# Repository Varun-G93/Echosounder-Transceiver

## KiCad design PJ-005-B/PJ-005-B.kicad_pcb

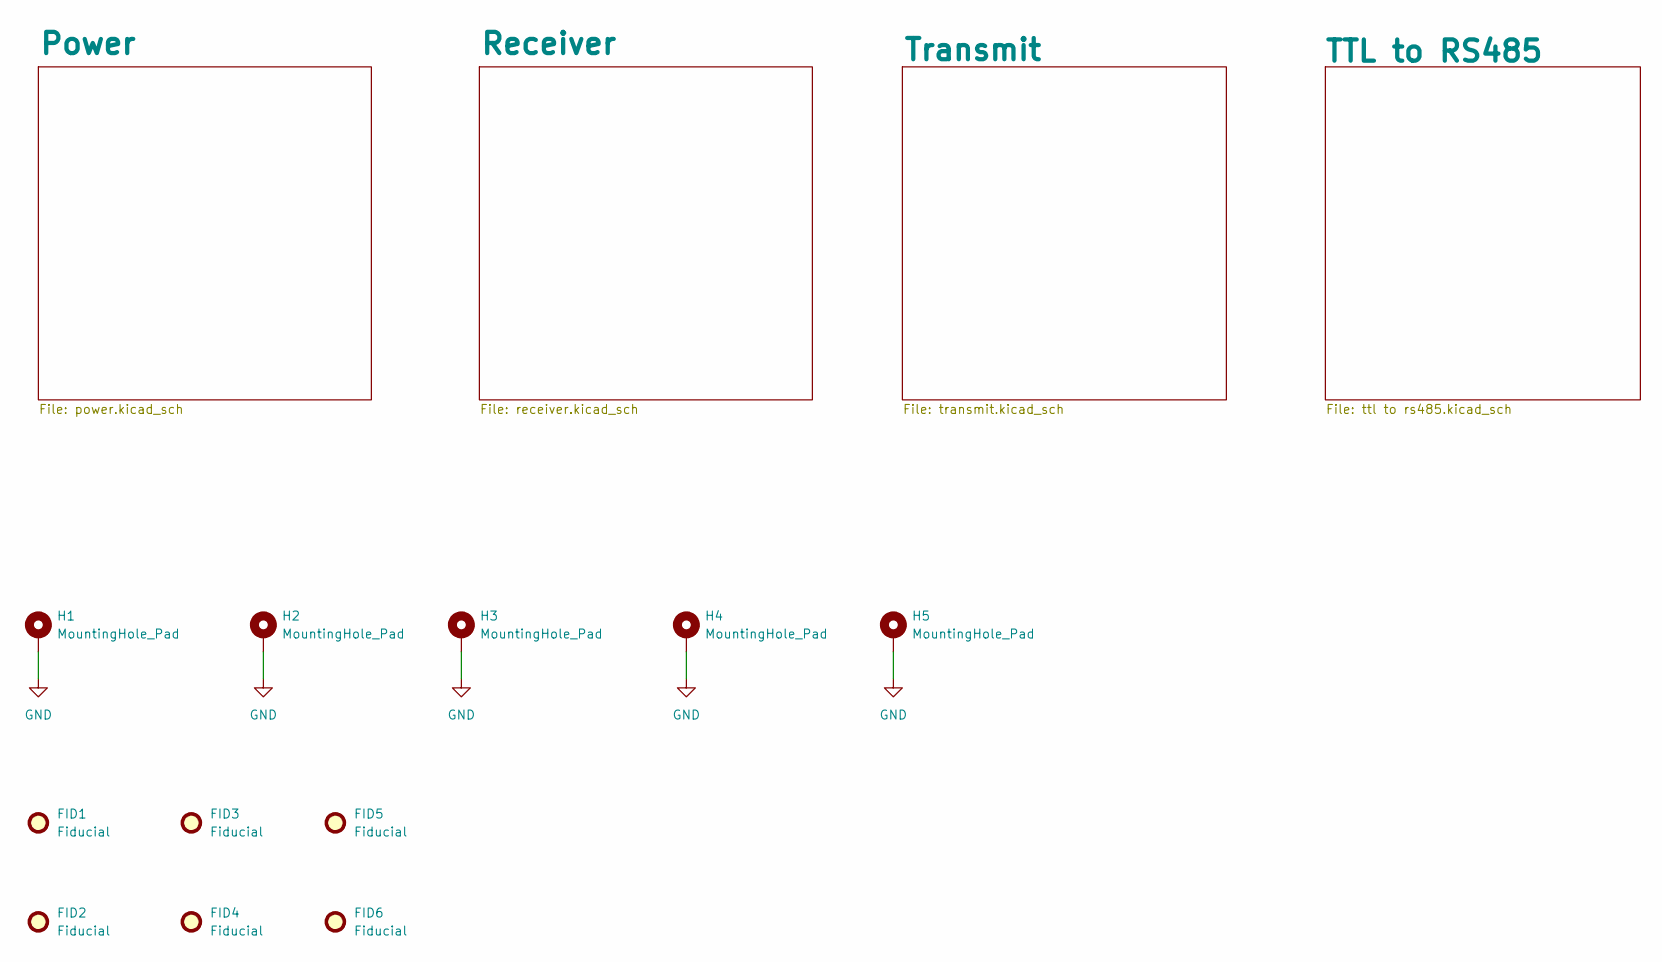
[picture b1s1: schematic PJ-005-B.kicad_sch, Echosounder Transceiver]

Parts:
FID1, FID2, FID3, FID4, FID5, FID6: Fiducial; Fiducial_0.5mm_Mask1mm
H1, H2, H3, H4, H5: MountingHole_Pad; MountingHole_3.2mm_M3_DIN965_Pad

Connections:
GND: H1.1, H2.1, H3.1, H4.1, H5.1; also elsewhere on the board

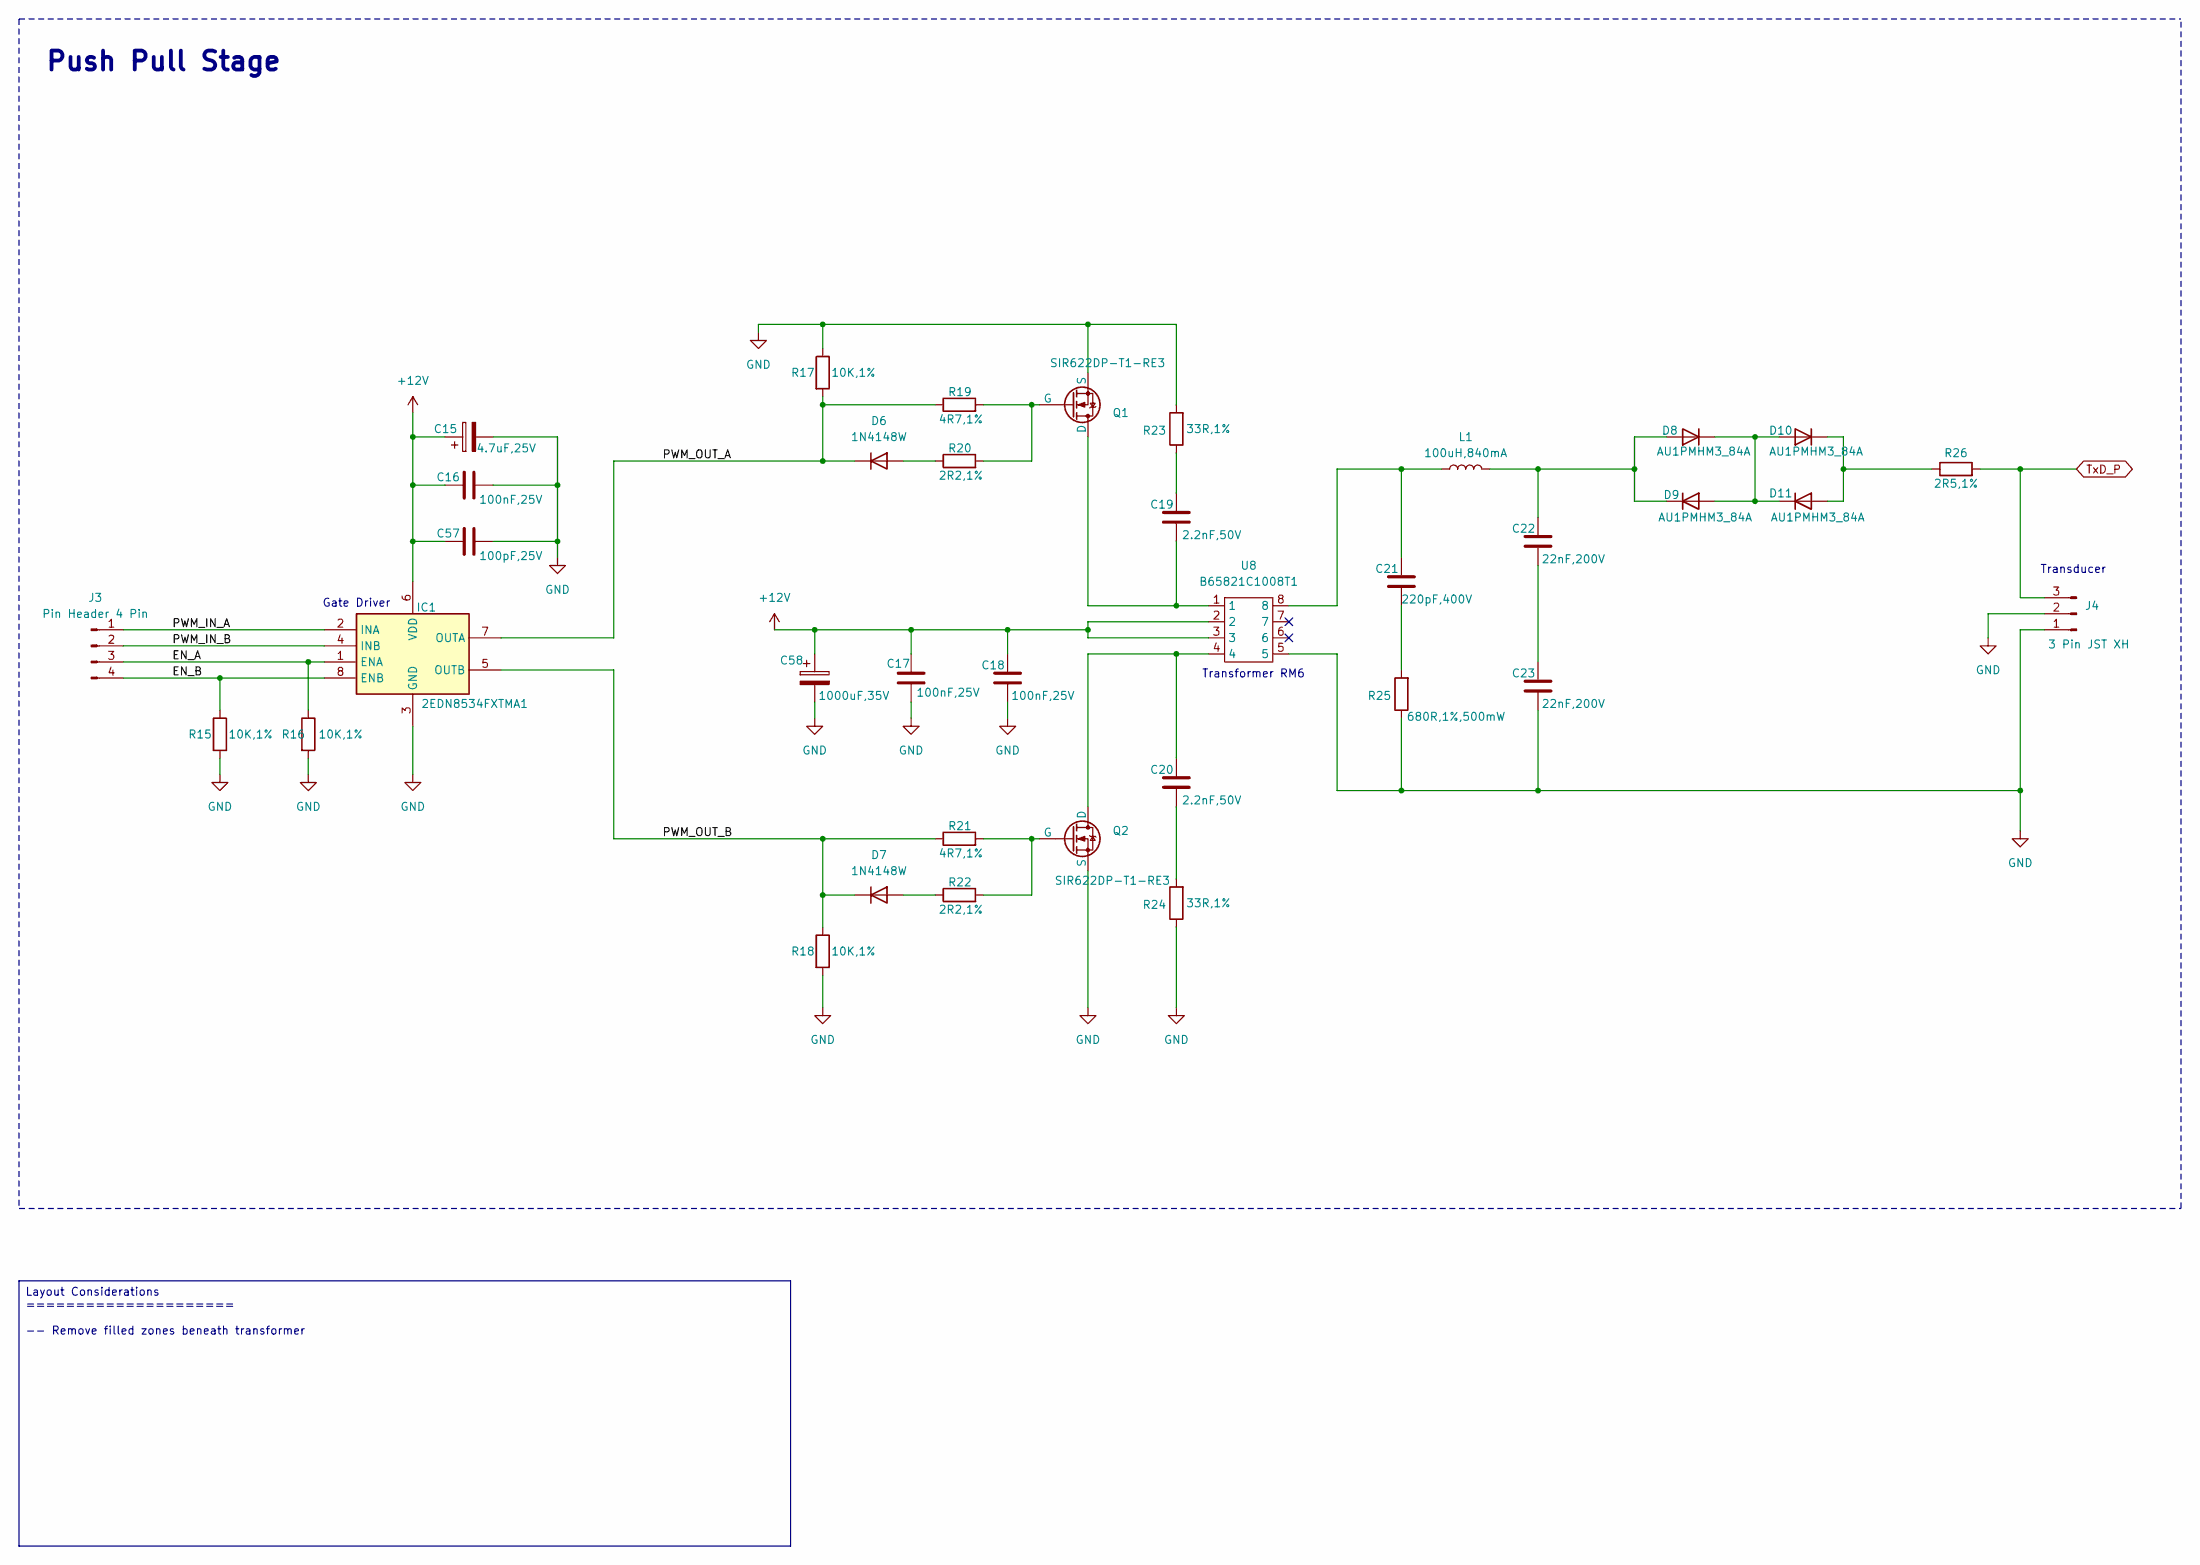
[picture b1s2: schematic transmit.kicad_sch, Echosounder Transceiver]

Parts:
C15: 4.7uF,25V; C1206; ManufacturerPartNumber TAJA475K025RNJ
C16, C17, C18: 100nF,25V; C0603
C19, C20: 2.2nF,50V; C0603
C21: 220pF,400V; C0603
C22, C23: 22nF,200V; C0603
C57: 100pF,25V; C0603
C58: 1000uF,35V; CP_Radial_D8.0mm_P3.50mm; ManufacturerPartNumber EEUFR1C102LJ
D6, D7: 1N4148W; SOD-123; ManufacturerPartNumber 1N4148W
D8, D9, D10, D11: AU1PMHM3_84A; AU1PMHM384A; ManufacturerPartNumber AU1PMHM3_84A
IC1: 2EDN8534FXTMA1; SOIC127P602X173-8N; ManufacturerPartNumber 2EDN8534FXTMA1
J3: Pin Header 4 Pin; PinHeader_1x04_P2.54mm_Vertical
J4: 3 Pin JST XH; JST_XH_B3B-XH-A_1x03_P2.50mm_Vertical
L1: 100uH,840mA; INDPM4040X300N; ManufacturerPartNumber ASPI-4030S-330M-T
Q1, Q2: SIR622DP-T1-RE3; SIR622DPT1RE3; ManufacturerPartNumber SIR622DP-T1-RE3
R15, R16, R17, R18: 10K,1%; R0603
R19, R21: 4R7,1%; R0603
R20, R22: 2R2,1%; R0603
R23, R24: 33R,1%; R0603
R25: 680R,1%,500mW; R0603
R26: 2R5,1%; R0603
U8: B65821C1008T1; RM6; ManufacturerPartNumber B65821C1008T1

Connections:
+12V: C15.1, C16.2, C17.1, C18.1, C57.2, C58.1, IC1.6 (VDD), U8.2, U8.3; also elsewhere on the board
/Transmit/EN_A: IC1.1 (ENA), J3.3, R16.1
/Transmit/EN_B: IC1.8 (ENB), J3.4, R15.1
/Transmit/PWM_IN_A: IC1.2 (INA), J3.1
/Transmit/PWM_IN_B: IC1.4 (INB), J3.2
/Transmit/PWM_OUT_A: D6.1 (K), IC1.7 (OUTA), R17.2, R19.1
/Transmit/PWM_OUT_B: D7.1 (K), IC1.5 (OUTB), R18.1, R21.1
GND: C15.2, C16.1, C17.2, C18.2, C23.2, C57.1, C58.2, IC1.3 (GND), J4.1, J4.2, Q1.2 (S), Q2.2 (S), R15.2, R16.2, R17.1, R18.2, R23.2, R24.1, R25.1, U8.5; also elsewhere on the board
unnamed: C19.1, R23.1
unnamed: C20.2, R24.2
unnamed: C21.1, L1.1, U8.8
unnamed: C21.2, R25.2
unnamed: C22.2, C23.1
unnamed: D6.2 (A), R20.1
unnamed: D7.2 (A), R22.1
unnamed: C22.1, D8.2 (A), D9.1 (K), L1.2
unnamed: D8.1 (K), D9.2 (A), D10.2 (A), D11.1 (K)
unnamed: D10.1 (K), D11.2 (A), R26.1
unnamed: C19.2, Q1.3 (D), U8.1
unnamed: Q1.1 (G), R19.2, R20.2
unnamed: C20.1, Q2.3 (D), U8.4
unnamed: Q2.1 (G), R21.2, R22.2
TxD_P: J4.3, R26.2; also elsewhere on the board

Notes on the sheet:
Transducer
Gate Driver
Push Pull Stage
Transformer RM6
Layout Considerations ===================== -- Remove filled zones beneath transformer

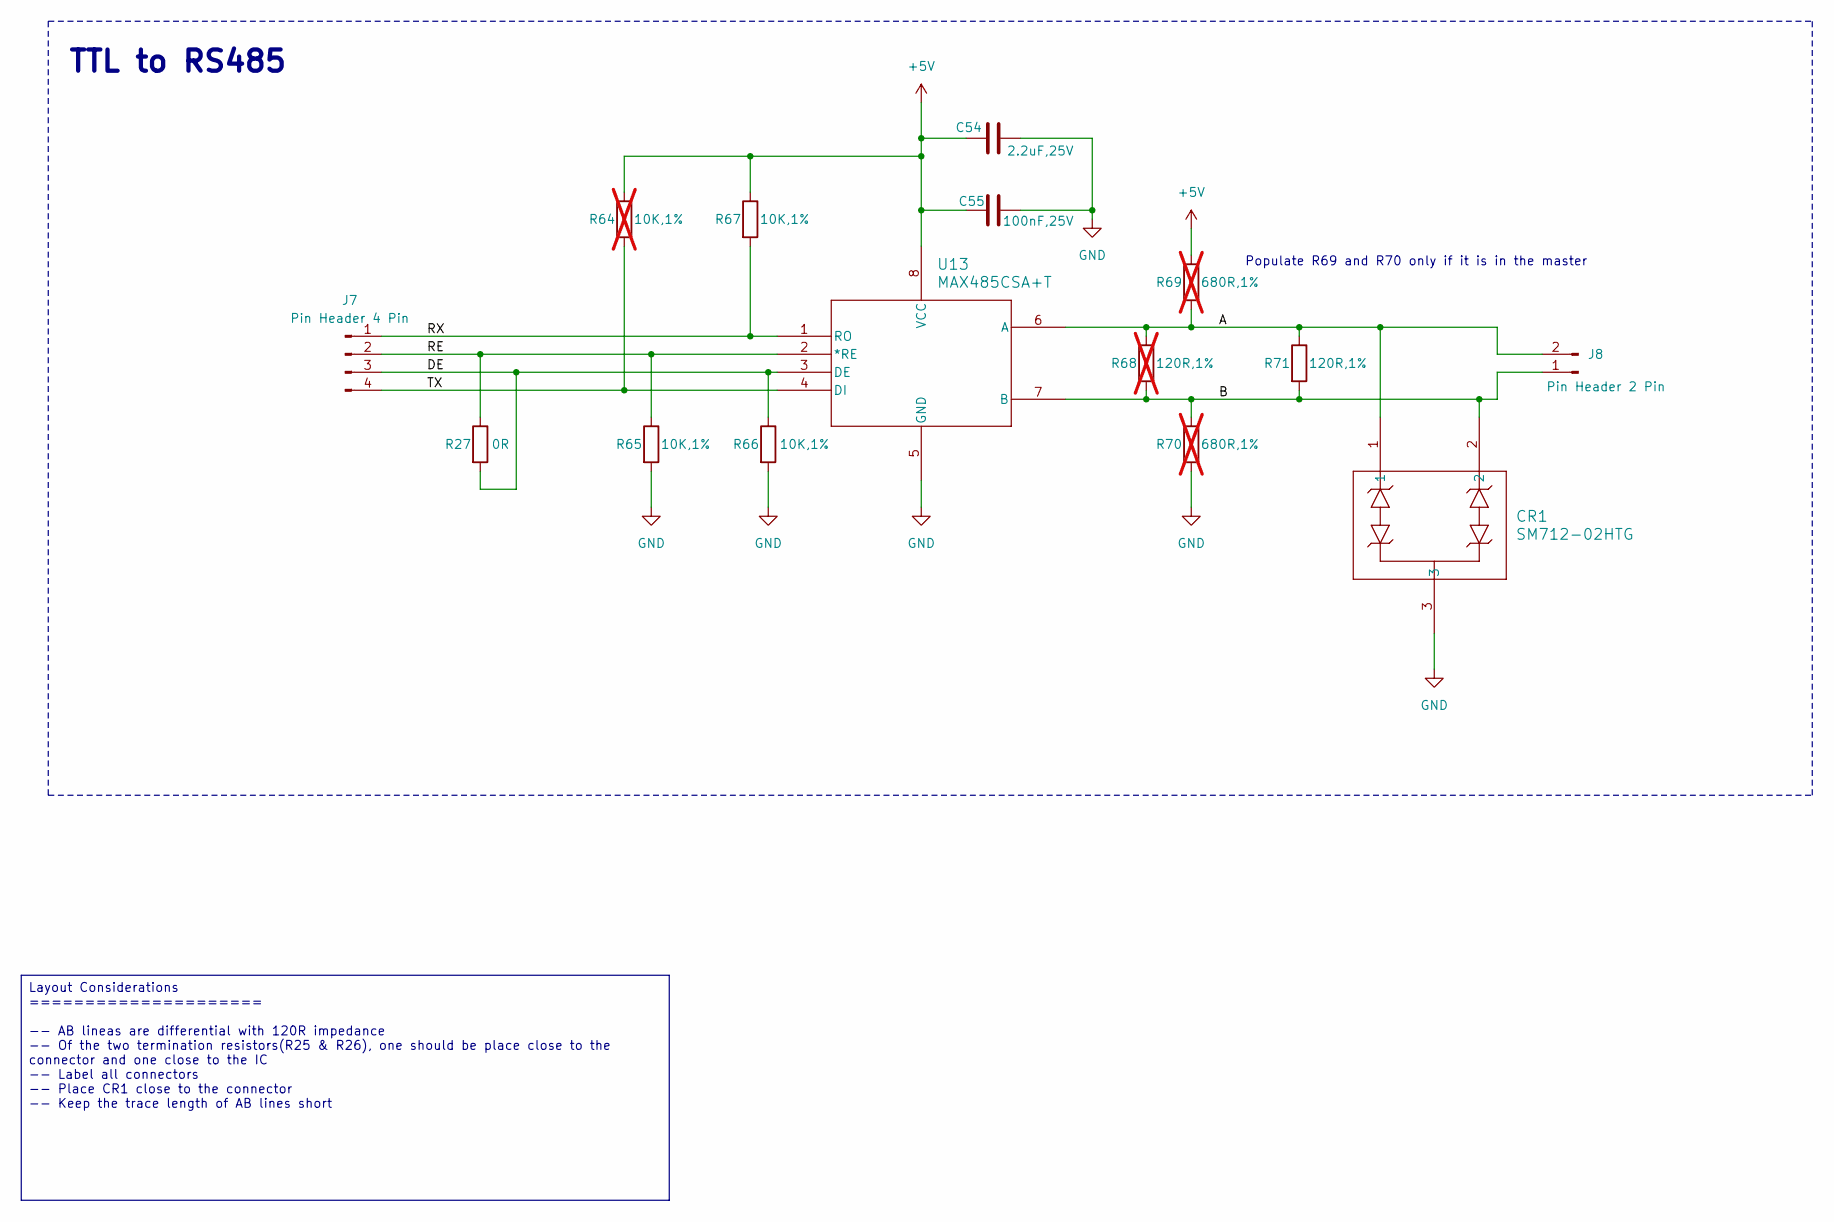
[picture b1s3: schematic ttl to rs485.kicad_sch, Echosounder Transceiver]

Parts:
C54: 2.2uF,25V; C0603
C55: 100nF,25V; C0603
CR1: SM712-02HTG; SOT-23-3; ManufacturerPartNumber SM712-02HTG
J7: Pin Header 4 Pin; PinHeader_1x04_P2.54mm_Vertical
J8: Pin Header 2 Pin; PinHeader_1x02_P2.54mm_Vertical
R27: 0R; R0603
R64: 10K,1%; R0603; not fitted
R65, R66, R67: 10K,1%; R0603
R68: 120R,1%; R0603; not fitted
R69, R70: 680R,1%; R0603; not fitted
R71: 120R,1%; R0603
U13: MAX485CSA+T; SOIC-8-5.3x5.3x1.27; ManufacturerPartNumber MAX485CSA+T

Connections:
+5V: C54.1, C55.1, R64.1, R67.1, R69.1, U13.8 (VCC); also elsewhere on the board
/TTL to RS485/A: CR1.1, J8.2, R68.1, R69.2, R71.1, U13.6 (A)
/TTL to RS485/B: CR1.2, J8.1, R68.2, R70.1, R71.2, U13.7 (B)
/TTL to RS485/DE: J7.3, R27.2, R66.1, U13.3 (DE)
/TTL to RS485/RE: J7.2, R27.1, R65.1, U13.2 (*RE)
/TTL to RS485/RX: J7.1, R67.2, U13.1 (RO)
/TTL to RS485/TX: J7.4, R64.2, U13.4 (DI)
GND: C54.2, C55.2, CR1.3, R65.2, R66.2, R70.2, U13.5 (GND); also elsewhere on the board

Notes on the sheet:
TTL to RS485
Populate R69 and R70 only if it is in the master
Layout Considerations ===================== -- AB lineas are differential with 120R impedance -- Of the two termination resistors(R25 & R26), one should be place close to the connector and one close to the IC -- Label all connectors -- Place CR1 close to the connector -- Keep the trace length of AB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

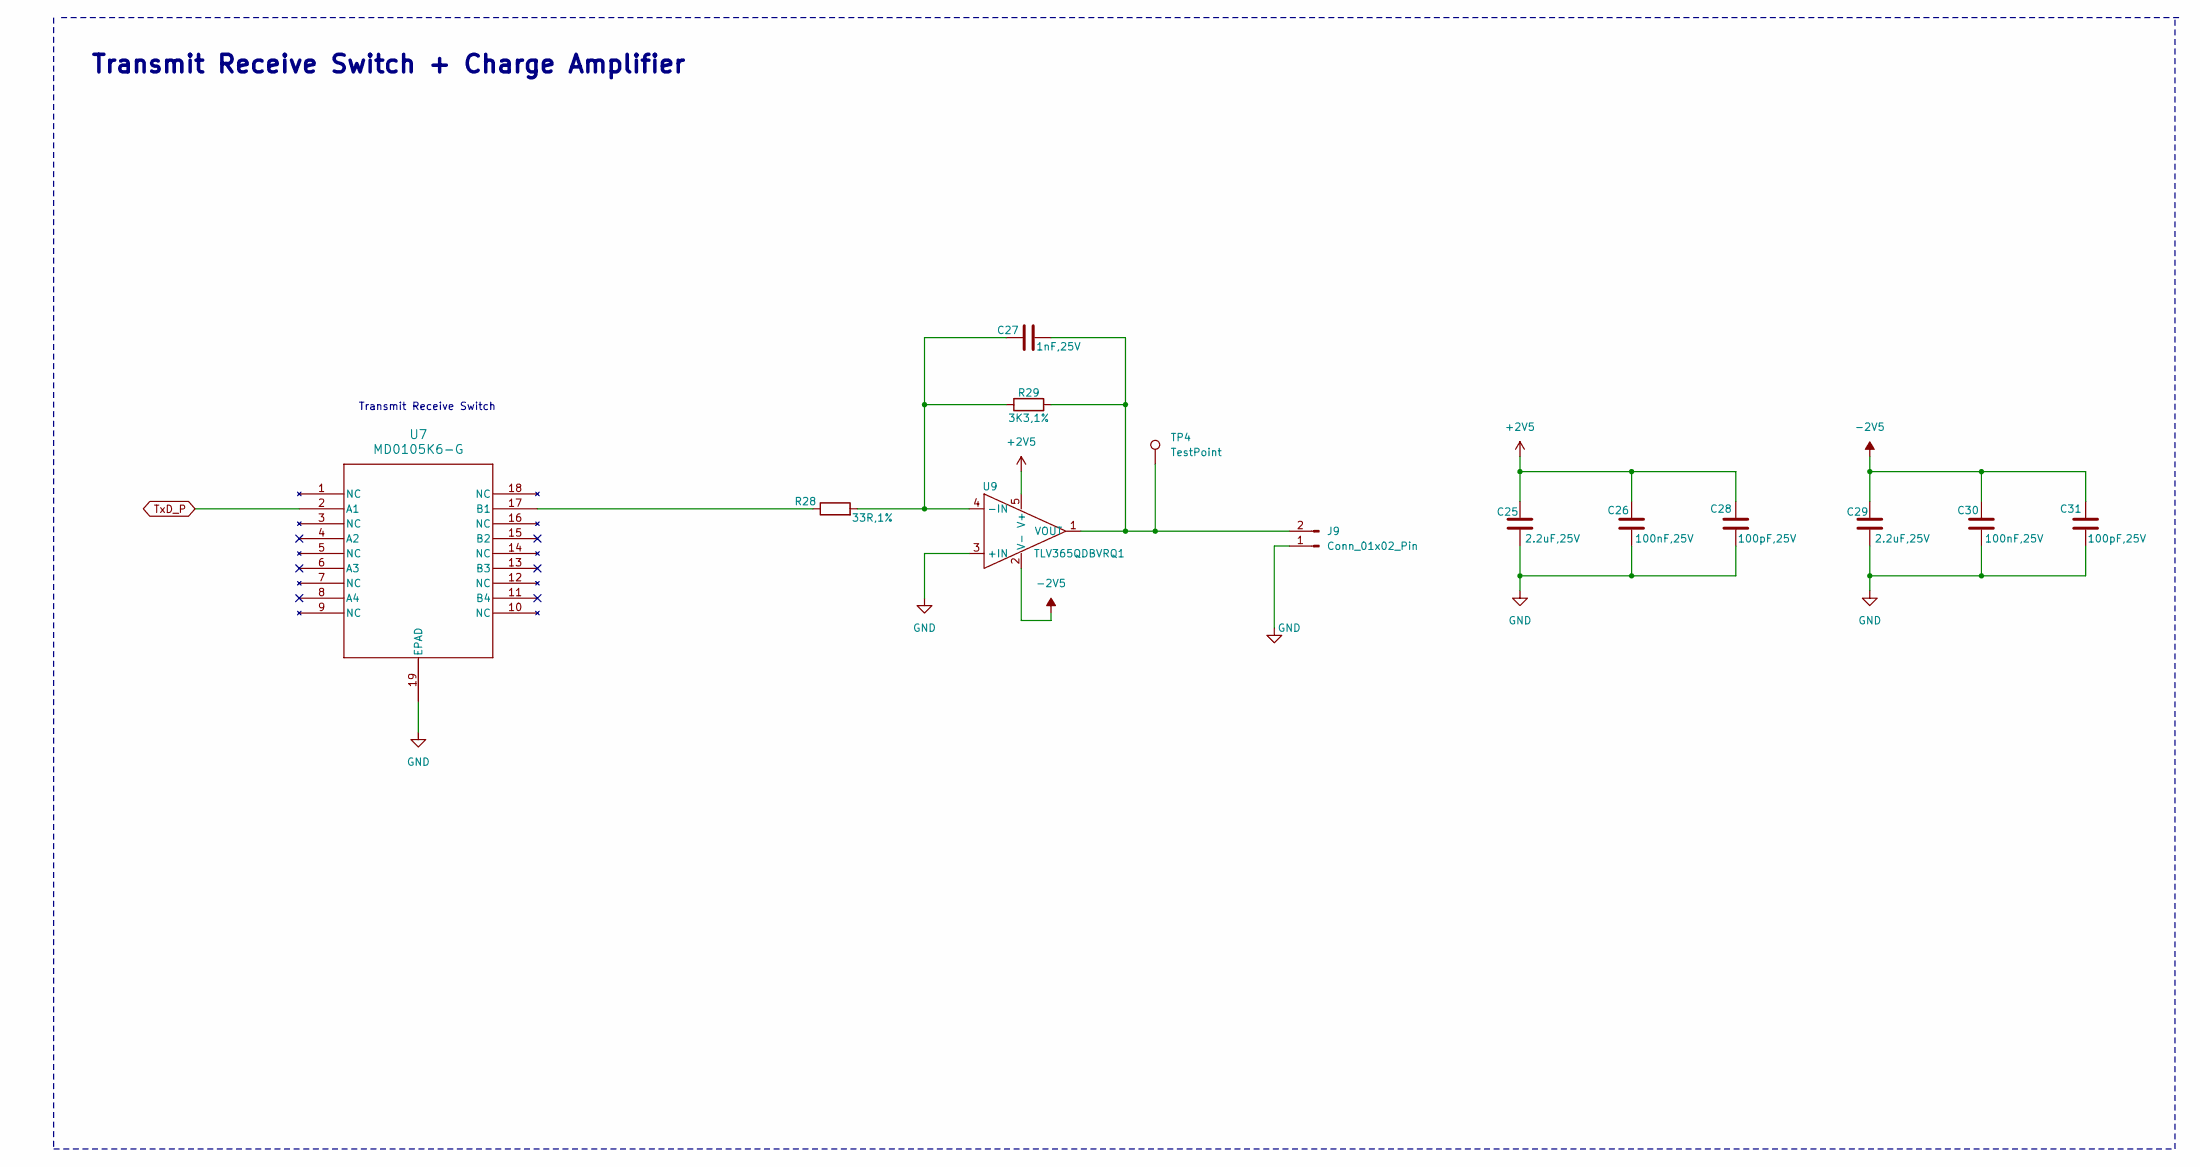
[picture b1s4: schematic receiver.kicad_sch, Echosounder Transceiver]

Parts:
C25, C29: 2.2uF,25V; C0603
C26, C30: 100nF,25V; C0603
C27: 1nF,25V; C0603
C28, C31: 100pF,25V; C0603
J9: Conn_01x02_Pin; PinHeader_1x02_P2.54mm_Vertical
R28: 33R,1%; R0603
R29: 3K3,1%; R0603
TP4: TestPoint; TestPoint_Pad_1.0x1.0mm
U7: MD0105K6-G; DFN18; ManufacturerPartNumber MD0105K6-G
U9: TLV365QDBVRQ1; SOT-23-5; ManufacturerPartNumber TLV365QDBVRQ1

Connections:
+2V5: C25.1, C26.2, C28.2, U9.5 (V+); also elsewhere on the board
-2V5: C29.1, C30.2, C31.2, U9.2 (V-); also elsewhere on the board
GND: C25.2, C26.1, C28.1, C29.2, C30.1, C31.1, J9.1, U7.19 (EPAD), U9.3 (+IN); also elsewhere on the board
unnamed: C27.2, J9.2, R29.2, TP4.1, U9.1 (VOUT)
unnamed: R28.1, U7.17 (B1)
unnamed: C27.1, R28.2, R29.1, U9.4 (-IN)
TxD_P: U7.2 (A1); also elsewhere on the board

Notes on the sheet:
Transmit Receive Switch
Transmit Receive Switch + Charge Amplifier

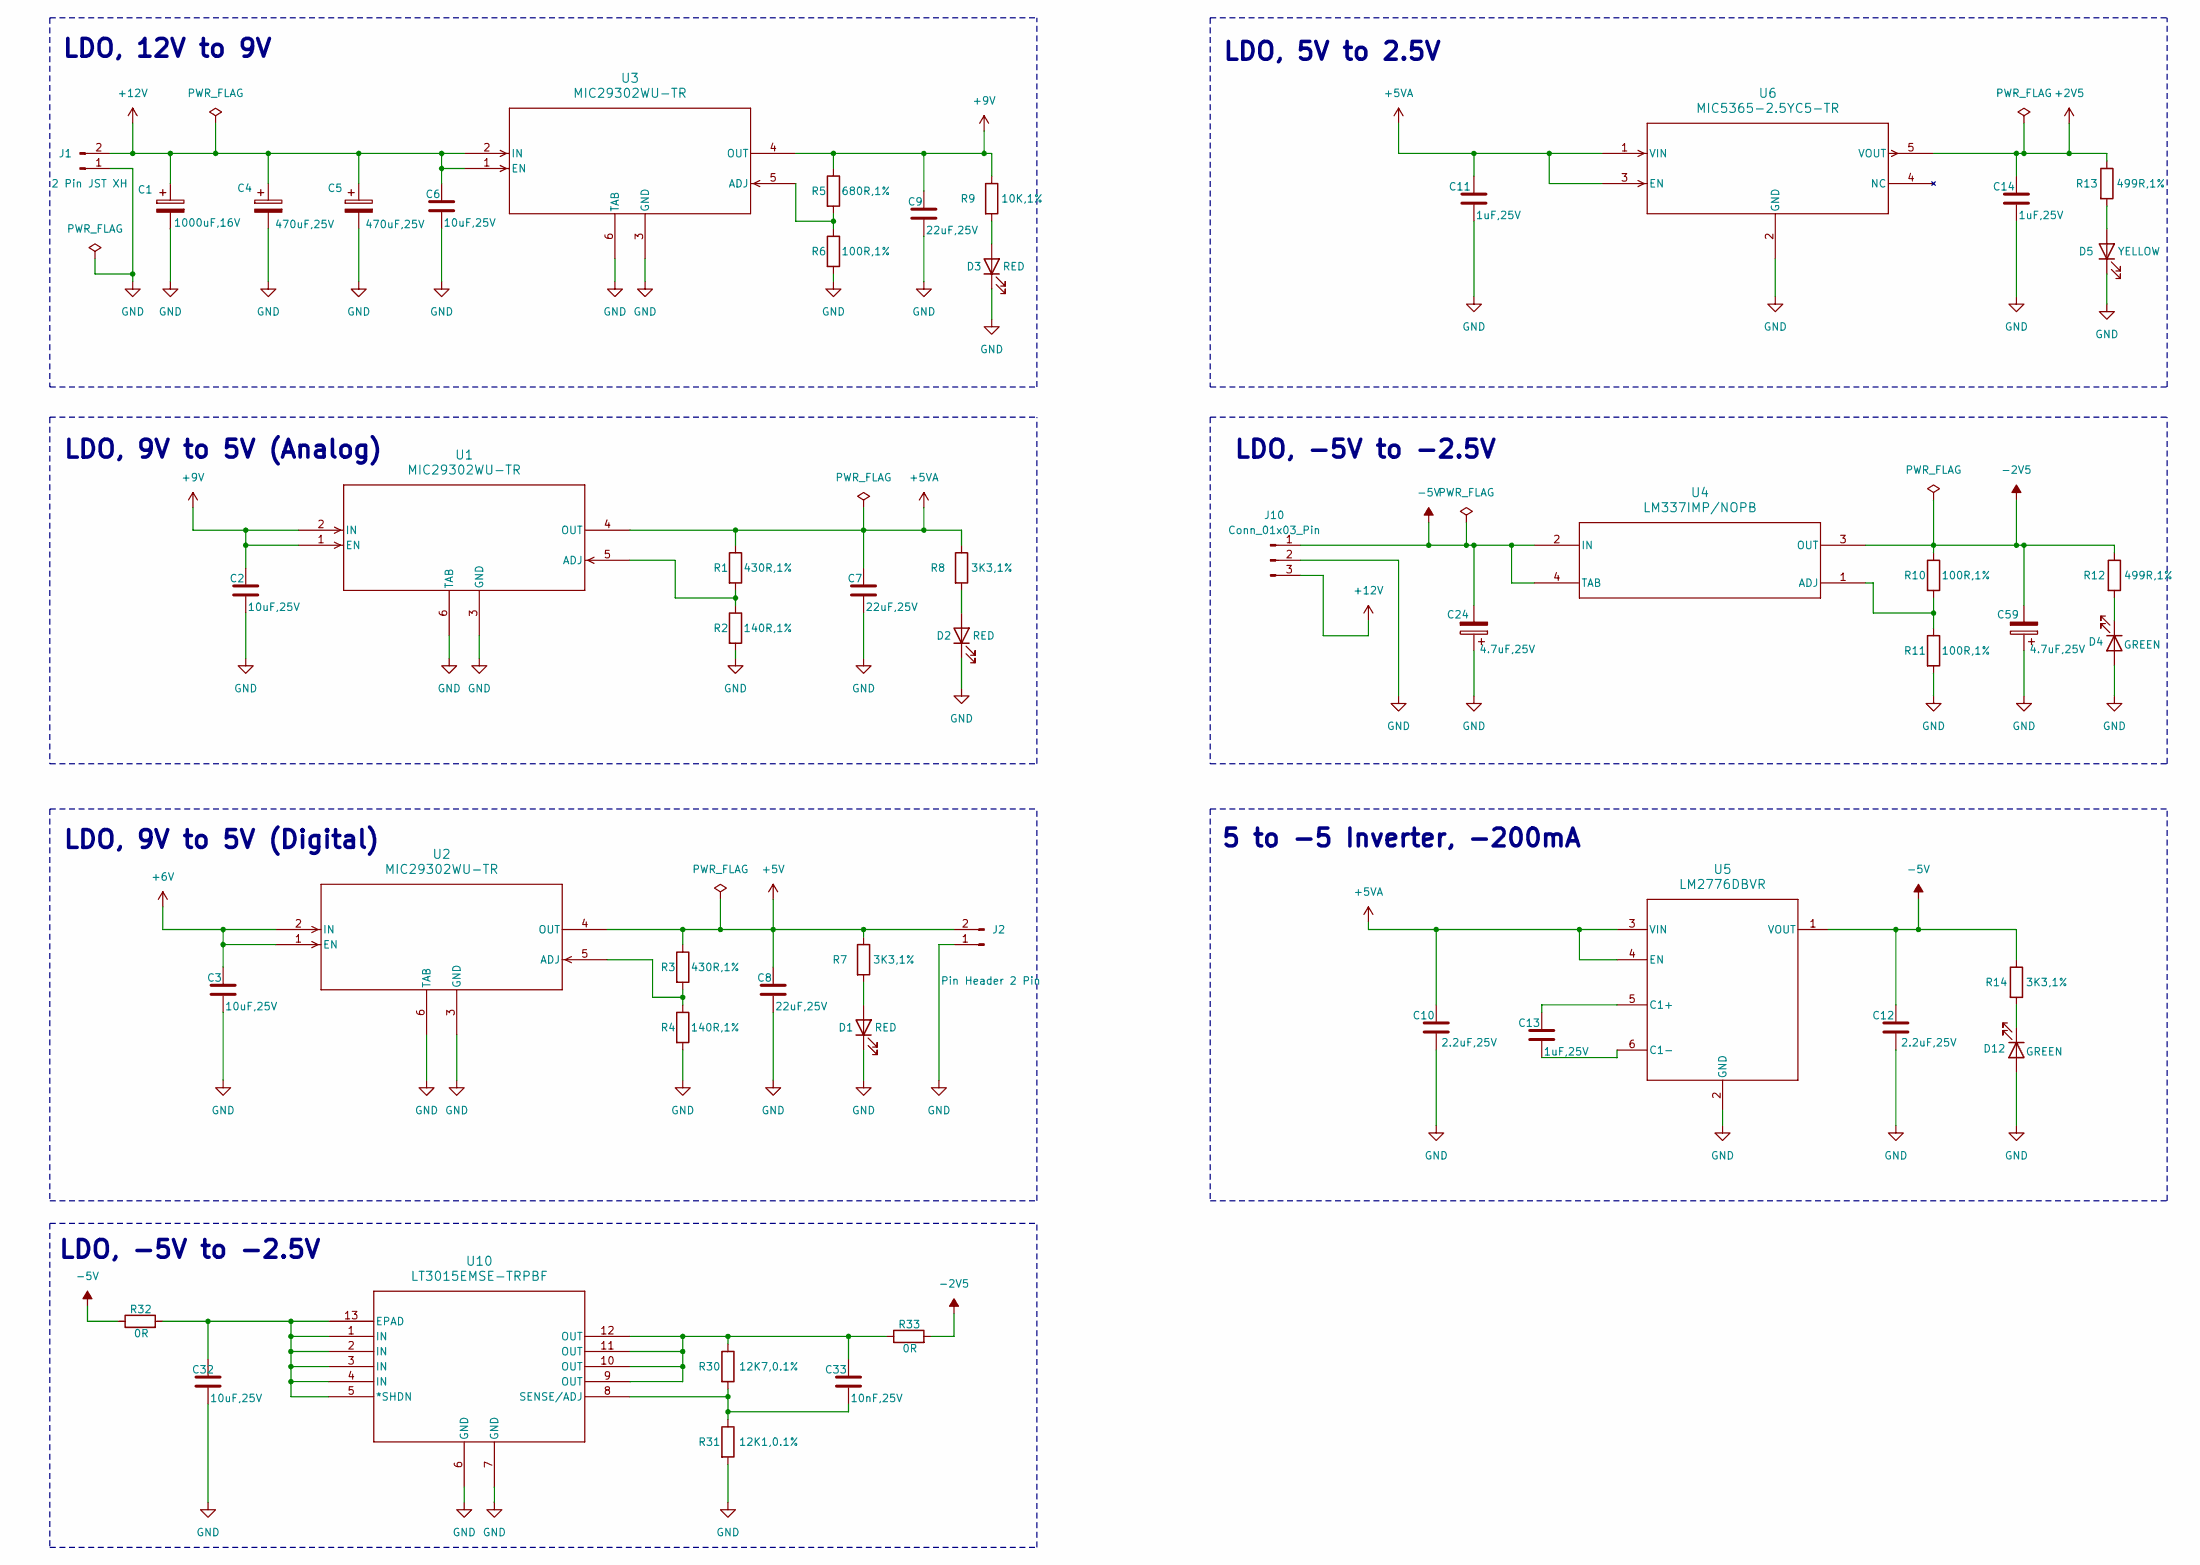
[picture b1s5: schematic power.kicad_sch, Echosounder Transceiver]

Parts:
C1: 1000uF,16V; CP_Radial_D8.0mm_P3.50mm; ManufacturerPartNumber EEUFR1C102LJ
C2, C3, C6, C32: 10uF,25V; C0603
C4, C5: 470uF,25V; CP_Radial_D8.0mm_P3.50mm; ManufacturerPartNumber RET0816471M025B
C7, C8, C9: 22uF,25V; C0603
C10, C12: 2.2uF,25V; C0603
C11, C13, C14: 1uF,25V; C0603
C24, C59: 4.7uF,25V; C1206; ManufacturerPartNumber TAJA475K025RNJ
C33: 10nF,25V; C0603
D1, D2, D3: RED; LED_0603_1608Metric
D4, D12: GREEN; LED_0603_1608Metric
D5: YELLOW; LED_0603_1608Metric
J1: 2 Pin JST XH; JST_XH_B2B-XH-A_1x02_P2.50mm_Vertical
J2: Pin Header 2 Pin; PinHeader_1x02_P2.54mm_Vertical
J10: Conn_01x03_Pin; PinHeader_1x03_P2.54mm_Vertical
R1, R3: 430R,1%; R0603
R2, R4: 140R,1%; R0603
R5: 680R,1%; R0603
R6, R10, R11: 100R,1%; R0603
R7, R8, R14: 3K3,1%; R0603
R9: 10K,1%; R0603
R12, R13: 499R,1%; R0603
R30: 12K7,0.1%; R0603
R31: 12K1,0.1%; R0603
R32, R33: 0R; R0603
U1, U2, U3: MIC29302WU-TR; TO-263-5; ManufacturerPartNumber MIC29302WU-TR
U4: LM337IMP/NOPB; SOT-223; ManufacturerPartNumber LM337IMP/NOPB
U5: LM2776DBVR; SOT23-6; ManufacturerPartNumber LM2776DBVR
U6: MIC5365-2.5YC5-TR; SC-70; ManufacturerPartNumber MIC5365-2.5YC5-TR
U10: LT3015EMSE-TRPBF; MSOP-12; ManufacturerPartNumber LT3015EMSE-TRPBF

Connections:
+2V5: C14.1, R13.1, U6.5 (VOUT); also elsewhere on the board
+5V: C8.1, J2.2, R3.1, R7.1, U2.4 (OUT); also elsewhere on the board
+5VA: C7.1, C10.1, C11.1, R1.1, R8.1, U1.4 (OUT), U5.3 (VIN), U5.4 (EN), U6.1 (VIN), U6.3 (EN)
+6V: C3.1, U2.1 (EN), U2.2 (IN)
+9V: C2.1, C9.1, R5.1, R9.1, U1.1 (EN), U1.2 (IN), U3.4 (OUT)
+12V: C1.1, C4.1, C5.1, C6.1, J1.2, J10.3, U3.1 (EN), U3.2 (IN); also elsewhere on the board
-2V5: C59.2, R10.1, R12.1, R33.2, U4.3 (OUT); also elsewhere on the board
-5V: C12.1, C24.2, J10.1, R14.1, R32.1, U4.2 (IN), U4.4 (TAB), U5.1 (VOUT)
GND: C1.2, C2.2, C3.2, C4.2, C5.2, C6.2, C7.2, C8.2, C9.2, C10.2, C11.2, C12.2, C14.2, C24.1, C32.2, C59.1, D1.1 (K), D2.1 (K), D3.1 (K), D4.2 (A), D5.1 (K), D12.2 (A), J1.1, J2.1, J10.2, R2.2, R4.2, R6.2, R11.2, R31.2, U1.3 (GND), U1.6 (TAB), U2.3 (GND), U2.6 (TAB), U3.3 (GND), U3.6 (TAB), U5.2 (GND), U6.2 (GND), U10.6 (GND), U10.7 (GND); also elsewhere on the board
unnamed: C33.1, R30.1, R33.1, U10.9 (OUT), U10.10 (OUT), U10.11 (OUT), U10.12 (OUT)
unnamed: D1.2 (A), R7.2
unnamed: D2.2 (A), R8.2
unnamed: D3.2 (A), R9.2
unnamed: D4.1 (K), R12.2
unnamed: D5.2 (A), R13.2
unnamed: D12.1 (K), R14.2
unnamed: R1.2, R2.1, U1.5 (ADJ)
unnamed: R3.2, R4.1, U2.5 (ADJ)
unnamed: R5.2, R6.1, U3.5 (ADJ)
unnamed: R10.2, R11.1, U4.1 (ADJ)
unnamed: C13.1, U5.5 (C1+)
unnamed: C13.2, U5.6 (C1-)
unnamed: C32.1, R32.2, U10.1 (IN), U10.2 (IN), U10.3 (IN), U10.4 (IN), U10.5 (*SHDN), U10.13 (EPAD)
unnamed: C33.2, R30.2, R31.1, U10.8 (SENSE/ADJ)

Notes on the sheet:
5 to -5 Inverter, -200mA
LDO, -5V to -2.5V
LDO, 9V to 5V (Analog)
LDO, 5V to 2.5V
LDO, 12V to 9V
LDO, 9V to 5V (Digital)

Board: 2 copper layers, 127 parts (49 on the bottom side), 54 nets, no tracks yet.

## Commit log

2026-04-06 Echosounder Transceiver PCB
    -- Regulator
    -- Receiver
    -- Transmitter
2026-04-06 Transmitter
    -- Preamp 9.5dB gain
    -- Power amp 6dB gain
2026-04-10 -- Transmitter with pre-amp LM7171 and power amp LT1210 -- Receiver with charge amp-->inverting amp-->4th order filter-->Inverting amp-->buffer -- Power with LDO 12V to 9V, 9V to 6V, 6V to 5V, 5V to 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
2026-04-10 -- Receive stage with charge amp-->inverting amp-->BPF-->inverting amp-->buffer-->PGA-->buffer -- Transmit stage with push pull mosfet -- TTL to RS485 converter -- LDOs 12V to 9V, 9V to 6V, 6V to 5V,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
2026-04-11 no message
2026-04-11 Transceiver After Review
    -- Added bulk capacitors for -2.5V LDO
    -- Added 0R for shorting RE and DE in TTL to RS485
    -- Changed the snubber values in transformer primary to 2.2nF and 33R
    -- Removed the 10nF and 100K in parallel with the transducer
    -- Added 1000uF capacitor for transformer centre tap
    -- Added 100pF decoupling capacitor for gate driver IC
2026-04-11 -- Reference Voltage IC removed -- Receiver includes only transmit receive switch and charge amp -- Changes in snubber values -- Changes in pull-up and pull-down resistors
2026-04-13 Removed filter, inverting amplifiers, buffer and PGA
